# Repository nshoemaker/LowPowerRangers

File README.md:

# LowPowerRangers
###2D TOF RF Tracking from a Single Sensor Bar
####18-549 Capstone Project for Team 20
####Clayton Ritcher, Nora Shoemaker, and Shashwat Srivastava
#####For more information, check out our website
https://www.ece.cmu.edu/~ece549/spring16/team20/website/

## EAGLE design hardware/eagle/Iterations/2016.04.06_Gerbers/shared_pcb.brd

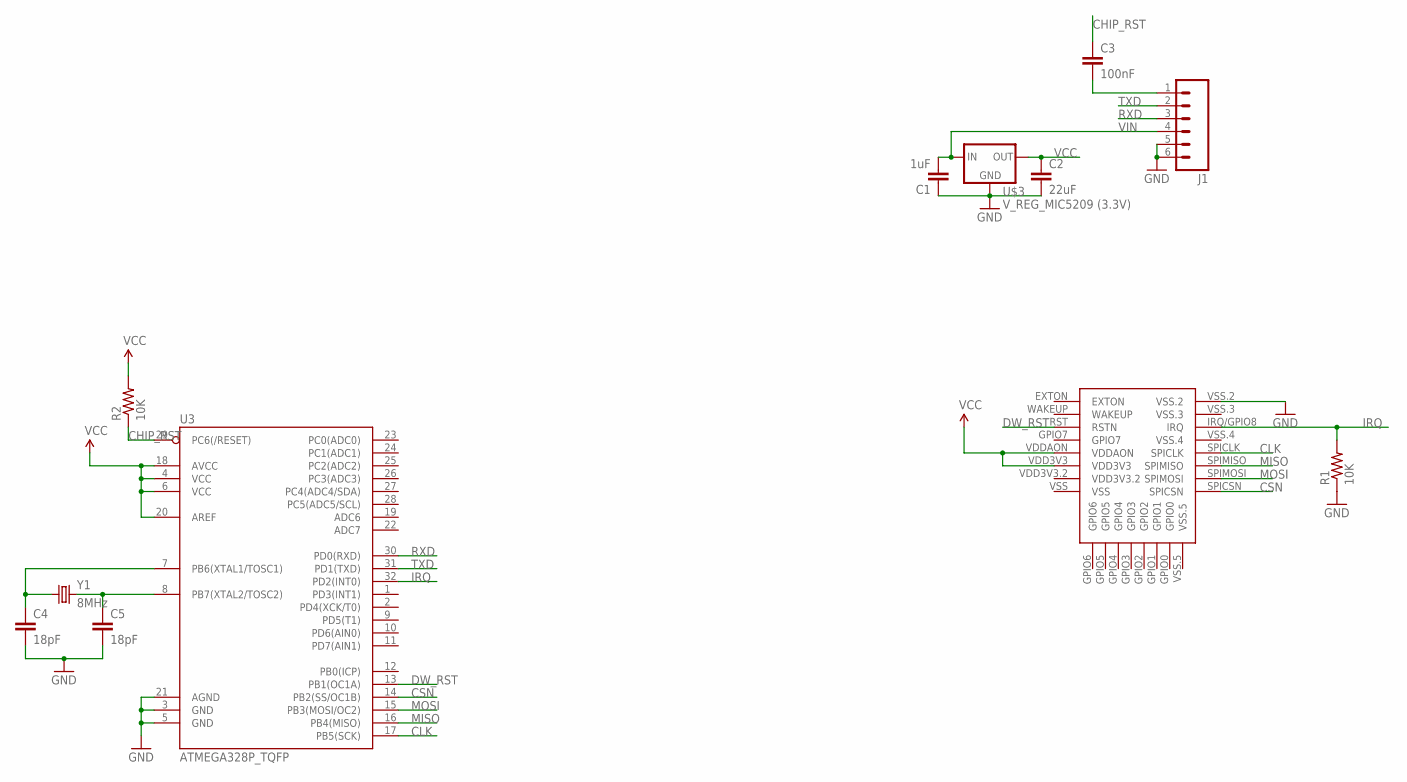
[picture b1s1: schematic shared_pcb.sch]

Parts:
C1: 1uF; 1206
C2: 22uF; 1206
C3: 100nF; 1206
C4, C5: 18pF; 1206
J1: M06LOCK; 1X06_LOCK
R1, R2: 10K; 1206
U3: ATMEGA328P_TQFP; TQFP32-08
U$1: DWM1000
U$3: V_REG_MIC5209 (3.3V); SOT223
Y1: 8MHz; CRYSTAL-TXC-7A

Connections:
CHIP_RST: C3.1, R2.1, U3.29 (PC6(/RESET))
CLK: U3.17 (PB5(SCK)), U$1.SPICLK
CSN: U3.14 (PB2(SS/OC1B)), U$1.SPICSN
DW_RST: U3.13 (PB1(OC1A)), U$1.RST (RSTN)
GND: C1.1, C2.2, C4.2, C5.2, J1.5, J1.6, R1.1, U3.3 (GND), U3.5 (GND), U3.21 (AGND), U$1.VSS.2, U$3.2 (GND)
IRQ: R1.2, U3.32 (PD2(INT0)), U$1.IRQ/GPIO8 (IRQ)
MISO: U3.16 (PB4(MISO)), U$1.SPIMISO
MOSI: U3.15 (PB3(MOSI/OC2)), U$1.SPIMOSI
unnamed: C3.2, J1.1
unnamed: C4.1, U3.7 (PB6(XTAL1/TOSC1)), Y1.P$1 (1)
unnamed: C5.1, U3.8 (PB7(XTAL2/TOSC2)), Y1.P$2 (2)
RXD: J1.3, U3.30 (PD0(RXD))
TXD: J1.2, U3.31 (PD1(TXD))
VCC: C2.1, R2.2, U3.4 (VCC), U3.6 (VCC), U3.18 (AVCC), U3.20 (AREF), U$1.VDD3V3, U$1.VDDAON, U$3.3 (OUT)
VIN: C1.2, J1.4, U$3.1 (IN)

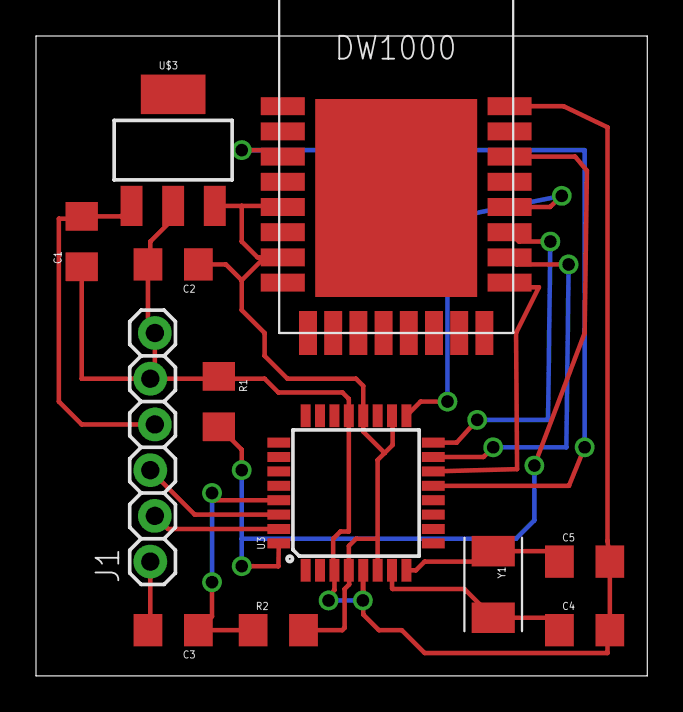
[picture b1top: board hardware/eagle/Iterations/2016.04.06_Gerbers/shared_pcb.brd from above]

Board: 2 copper layers, 34.0 x 35.5 mm, 12 parts (0 on the bottom side), 15 nets.

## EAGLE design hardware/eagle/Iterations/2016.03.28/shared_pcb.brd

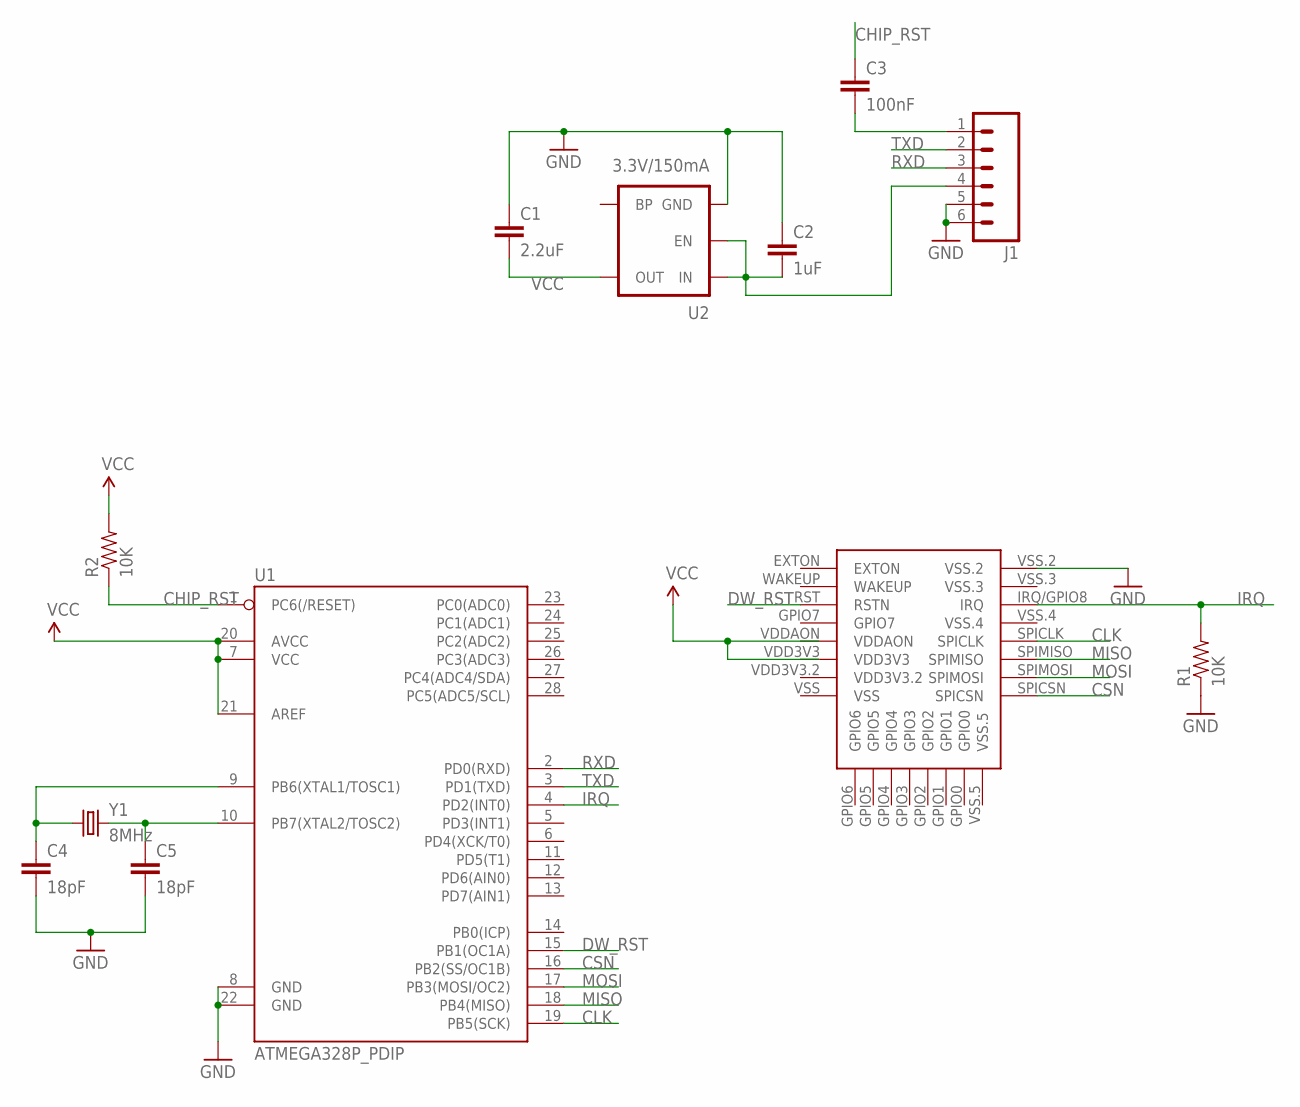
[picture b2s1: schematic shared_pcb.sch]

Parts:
C1: 2.2uF; 1206
C2: 1uF; 1206
C3: 100nF; 1206
C4, C5: 18pF; 1206
J1: M06LOCK; 1X06_LOCK
R1, R2: 10K; 1206
U1: ATMEGA328P_PDIP; DIL28-3
U2: 3.3V/150mA; SOT23-5
U$1: DWM1000
Y1: 8MHz; CRYSTAL-TXC-7A

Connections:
CHIP_RST: C3.1, R2.1, U1.1 (PC6(/RESET))
CLK: U1.19 (PB5(SCK)), U$1.SPICLK
CSN: U1.16 (PB2(SS/OC1B)), U$1.SPICSN
DW_RST: U1.15 (PB1(OC1A)), U$1.RST (RSTN)
GND: C1.1, C2.1, C4.2, C5.2, J1.5, J1.6, R1.1, U1.8 (GND), U1.22 (GND), U2.2 (GND), U$1.VSS.2
IRQ: R1.2, U1.4 (PD2(INT0)), U$1.IRQ/GPIO8 (IRQ)
MISO: U1.18 (PB4(MISO)), U$1.SPIMISO
MOSI: U1.17 (PB3(MOSI/OC2)), U$1.SPIMOSI
unnamed: C4.1, U1.9 (PB6(XTAL1/TOSC1)), Y1.P$1 (1)
unnamed: C2.2, J1.4, U2.1 (IN), U2.3 (EN)
unnamed: C3.2, J1.1
unnamed: C5.1, U1.10 (PB7(XTAL2/TOSC2)), Y1.P$2 (2)
RXD: J1.3, U1.2 (PD0(RXD))
TXD: J1.2, U1.3 (PD1(TXD))
VCC: C1.2, R2.2, U1.7 (VCC), U1.20 (AVCC), U1.21 (AREF), U2.5 (OUT)

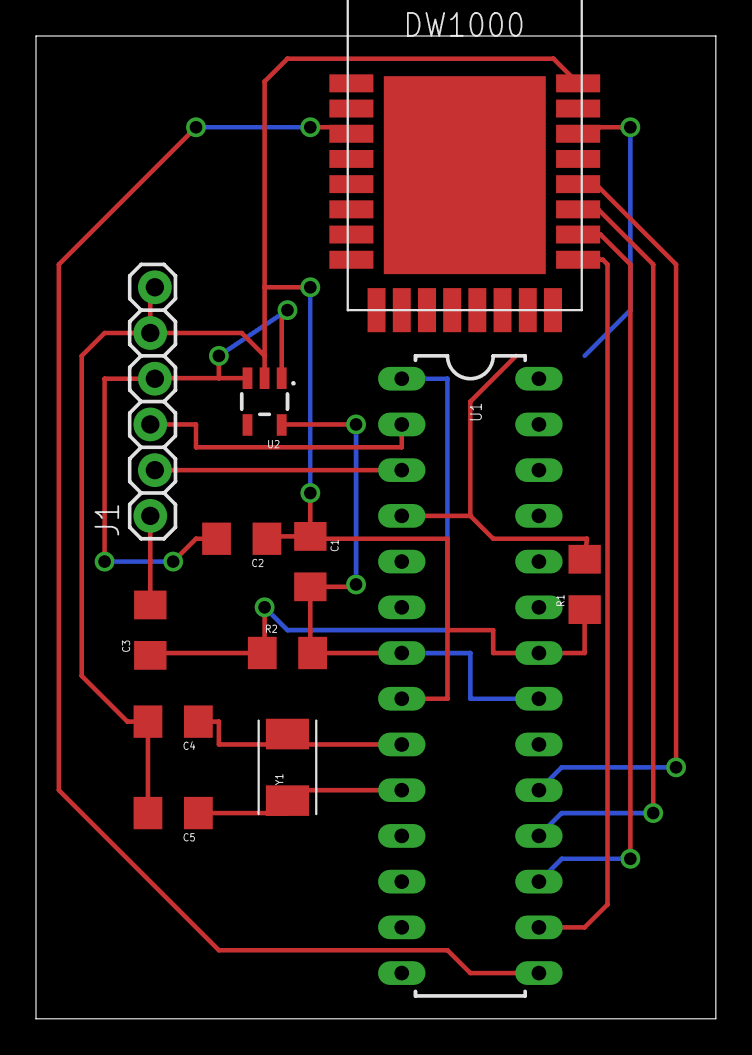
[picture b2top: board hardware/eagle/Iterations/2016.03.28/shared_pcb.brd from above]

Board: 2 copper layers, 37.8 x 54.6 mm, 12 parts (0 on the bottom side), 15 nets.

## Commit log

2016-02-16 Add logo
2016-02-16 Add other proposal images
2016-02-16 Add empty website template
2016-02-17 First stab at website sections
2016-02-17 Changed the banner.
2016-02-17 Giant docs section
2016-02-17 Recolored the banner.
2016-02-17 New sectioning done
2016-02-17 Add motivation and competative analysis
2016-02-18 Edited wording.
2016-02-18 Add parts list and requirements
2016-02-18 Add protocols
2016-02-18 Fix updates section
2016-02-18 Fix title
2016-02-19 Added UART and FTDI info. Also cleaned up a few of the images.
2016-02-22 Adding lab 3 code and MAKEFILE!!!!!!
2016-02-27 Adding skeleton code and makefiles for the bootloader and the tag/anchors. Also added directions for building/installing.
2016-02-28 Add test html file so it's not festering in the index file
2016-02-28 Add website update for 02/29/2016.
2016-02-28 Fix awk space in website making M akefile -> Makefile.
2016-02-29 Add webserver folder
2016-02-29 Running test server
2016-03-02 Added a simple Hello World for talking to the DWM1000s.
2016-03-04 Added offset reading and writing over SPI. Also added reading and writing of network and device address. The device address is passed through a command line argument to the makefile
2016-03-15 Adding initial schematic
2016-03-15 Adding DWM1000 eagle library file
2016-03-15 starting website for this week
2016-03-15 Made some changes in settings
2016-03-15 Added procfile and requirements
2016-03-15 First attempt deploying
2016-03-15 Trying to deploy to Heroku
2016-03-15 Made changes to settings
2016-03-15 Changed database settings
2016-03-15 Added database
2016-03-16 website (hopefully) done for this week
2016-03-17 Added all of the register file values needed. Compiles, but nothing is being done with them yet, really.
2016-03-18 Added network and address config to DW_init
2016-03-18 Added the code which is running on the Raspi for serial communication and talking to the website
2016-03-18 Interrupts seem to be working. Transmission is tentatively working, though I have not tried reception yet so who knows.
2016-03-19 Receiving is working!!!! Kinda. Fails after one message
2016-03-20 Handling reception errors better. No crashing but every other message is dropped.
2016-03-20 Reception works!!!!!!!!
2016-03-21 Website update 3/21
2016-03-26 Modified the DWM code to expose client callbacks for reception, failed reception, and transmission.
2016-03-28 Eagle schematic and layout
2016-03-29 Push sample
2016-03-29 Updated .gitignore with android files
2016-03-31 Create AppIdea,md
2016-03-31 3/28 weekly update
2016-03-31 Added images and start Android code
2016-03-31 Trying to show image on .md
2016-03-31 Update AppIdea,md
2016-04-01 Added timestamp helper functions.
2016-04-01 3/28 writeup adding app idea docs
2016-04-01 Website add use cases
2016-04-01 Website adding architecture
2016-04-01 Webiste add interaction diagrams
2016-04-01 Commit before trying new Makefile.
2016-04-02 Got reception working reliably!!!!
2016-04-02 Adding tinyserial files to replace hardwareserial.
2016-04-02 Commiting a messed up version to roll back.
2016-04-02 Fixed LDE load code.
2016-04-02 Again, committing a bad copy...
2016-04-02 RX delay and rx timeout are both working.
2016-04-02 Made the startup more reliable.
2016-04-02 Added a getTime method.
2016-04-02 Got anchor side code tentatively finished.
2016-04-03 Can make network calls and initialize Tags
2016-04-03 Added files as intial designs
2016-04-03 Finished tag and anchor code. Still using huge delays.
2016-04-03 Add schematic/layout backup
2016-04-03 Add schematic/layout with AVR Programmer
2016-04-03 Add schematic/layout for SMD without AVR
2016-04-03 Propogation time estimates are stable!!!! They still need antenna delay calibration.
2016-04-03 Pretty accurate! (20-30 cm at worse when under 5m).
2016-04-03 4/4/16 website update (everything but link to android code)
2016-04-03 Tag now moves with data from the server
2016-04-03 Can now move positions according to the information from the server
2016-04-04 Adding a logo bitmap for the pcb.
2016-04-04 Added a test for the app
2016-04-04 Fixed mismatched parantheses
2016-04-04 changed view to send theta as radians
2016-04-04 App works under good conditions. Need to test error tags
2016-04-04 Need to error check
2016-04-04 Add app link
2016-04-05 Added error checking
2016-04-05 Cleaned up the code
2016-04-05 Error toast when trying to add invalid Tag
2016-04-06 pcb-fix decoupling cap around voltage regulator
2016-04-06 Moving hardware files into folder
2016-04-06 pcb - moving other cap towards v reg
2016-04-06 pcb - adding silkscreen
2016-04-06 Adding cam file from class
2016-04-06 pcb - add gerber files for board to be printed
2016-04-06 pcb - add _TO_PRINT_ folder
2016-04-06 Moving old boards into Iterations folder
2016-04-06 Added resets of the DWM after each range.
2016-04-07 Added periodic resetting and bettor error handling.
    Tried a 35+ meter test and accuracy was within 10 cm.
2016-04-09 Fixed a typo in the Makefile
2016-04-10 Added command line options for antenna delays and made delays.txt to keep track of the delays for each board.
2016-04-11 Got dual-anchor ranging working!
2016-04-11 Updated delay tuning.
2016-04-11 Changed room size to 300 * 800
2016-04-11 Changed files to be able to read from the anchor tags
2016-04-11 Removed old non working files
2016-04-11 Added error checking for wifi when the raspi starts up
2016-04-11 Changed the testing code
2016-04-11 Modified webserver to add a timestamp
2016-04-11 Forgot to import transactions
2016-04-11 Changed hte db settings to run locally
2016-04-11 Add migration file
2016-04-16 Fixed the weird issue where the first anchor and the second anchor needed different antenna delays.
2016-04-16 Got rid of extra print statements
2016-04-18 Commiting udpated raspberry pi files
2016-04-18 Added scheduling for tasks and now takes average of values
2016-04-18 Added textView to show the theta and R values on screen
2016-04-18 Changed code so that calls to server run on separate thread
2016-04-18 Changed height and width to aspect ratio
2016-04-18 Changed timer to 3s instead of 300ms
2016-04-18 Updated the dwm rates to be much faster (10 Hz).
2016-04-18 Resetting the anchors on startup of raspi code.
2016-04-23 Got frid lines
2016-04-23 info only shows up when the tag is actually clicked
2016-04-23 Cleaned up UI a little
2016-04-23 Can now rotate screen
2016-04-25 Added a TextView to show size of boxes
2016-04-27 Add testing script
2016-04-27 Adjusted antenna delays for new tag enclosure
2016-04-27 Added a slight delay in the data gathering code to lessen effects of stale data.
2016-04-27 Updated data gathering code to report expected values.
2016-04-27 Changed number of points gathered in tests.
2016-04-29 Added smooth animations to the android app tag.
2016-04-29 Updated the android app to use our logo and name.
2016-04-29 Can now zoom and pan but the Tags dont move
2016-04-29 Current version of the app. About to start trying to only chage the room size
2016-04-29 Can do the new zoom idea but the text box mesasge is wrong
2016-04-29 Got the zoom scale to work correctly
2016-04-29 Got rid of averaging in raspi code.
2016-04-29 Changed the logo to non-copyrighted logo.
2016-04-29 Changed the name to a noncopyrighted name.
2016-04-29 Averages values for translationX and translationY
2016-04-29 Got popup window to work on Samsung phones too
2016-04-29 Changed the package name.
2016-04-29 Made the location textview update as the tag moves.
2016-04-29 Cleaned up the code slightly
2016-04-29 Made popup window rounded
2016-04-30 Can now take pictures and show them
2016-04-30 Now has a cancel button to leave picture and go back to Original page
2016-04-30 Can now take image, transform it and then succesfully return to the main menu
2016-04-30 Can now draw lines on the image and all the stuff. Need to fix the transformation
2016-04-30 Made the lines a lot more accurate. The transformation looks good now
2016-05-01 Fixed the issue with the picture
2016-05-01 Cleaned up the UI slightly
2016-05-05 The image now gets updated every 10 seconds but the UI is wrong
2016-05-05 Fixed everything except the tag is off
2016-05-05 Fixed everything except the tag height is wrong by the scale
2016-05-05 Added the drawable files
2016-05-08 Website updates
2016-05-08 Adding links to external docs
2016-05-09 Website update

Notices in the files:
parts and their libraries:
SparkFun-Capacitors: Licensing: Creative Commons ShareAlike 4.0 International - https://creativecommons.org/licenses/by-sa/4.0
